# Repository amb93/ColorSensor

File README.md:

# Color sensor
A compact device that helps the blind and color blind to differentiate between colors. The devices shows the color on the top screen and has an AUX plug for voice. Fully rechargable, lasting over 10 hours.

# Work progress

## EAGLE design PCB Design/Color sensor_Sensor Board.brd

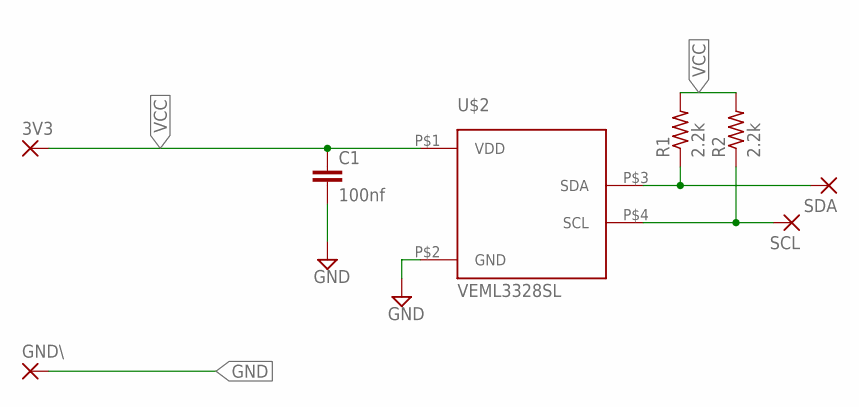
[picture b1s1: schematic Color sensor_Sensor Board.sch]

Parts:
3V3: SMD2; SMD1,27-2,54
C1: 100nf; C0805
GND\: SMD2; SMD1,27-2,54
R1, R2: 2.2k; R0805
SCL: SMD2; SMD1,27-2,54
SDA: SMD2; SMD1,27-2,54
U$2: VEML3328SL; OPLGA4SV

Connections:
GND: C1.2, GND\.1, U$2.P$2 (GND)
unnamed: R1.1, SDA.1, U$2.P$3 (SDA)
unnamed: R2.1, SCL.1, U$2.P$4 (SCL)
VCC: 3V3.1, C1.1, R1.2, R2.2, U$2.P$1 (VDD)

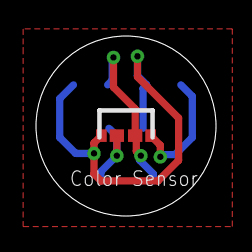
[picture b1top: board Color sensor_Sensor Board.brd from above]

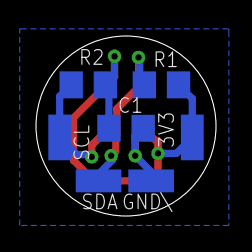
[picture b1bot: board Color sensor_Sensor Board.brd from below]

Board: 2 copper layers, 10.0 x 10.0 mm, 8 parts (7 on the bottom side), 4 nets.

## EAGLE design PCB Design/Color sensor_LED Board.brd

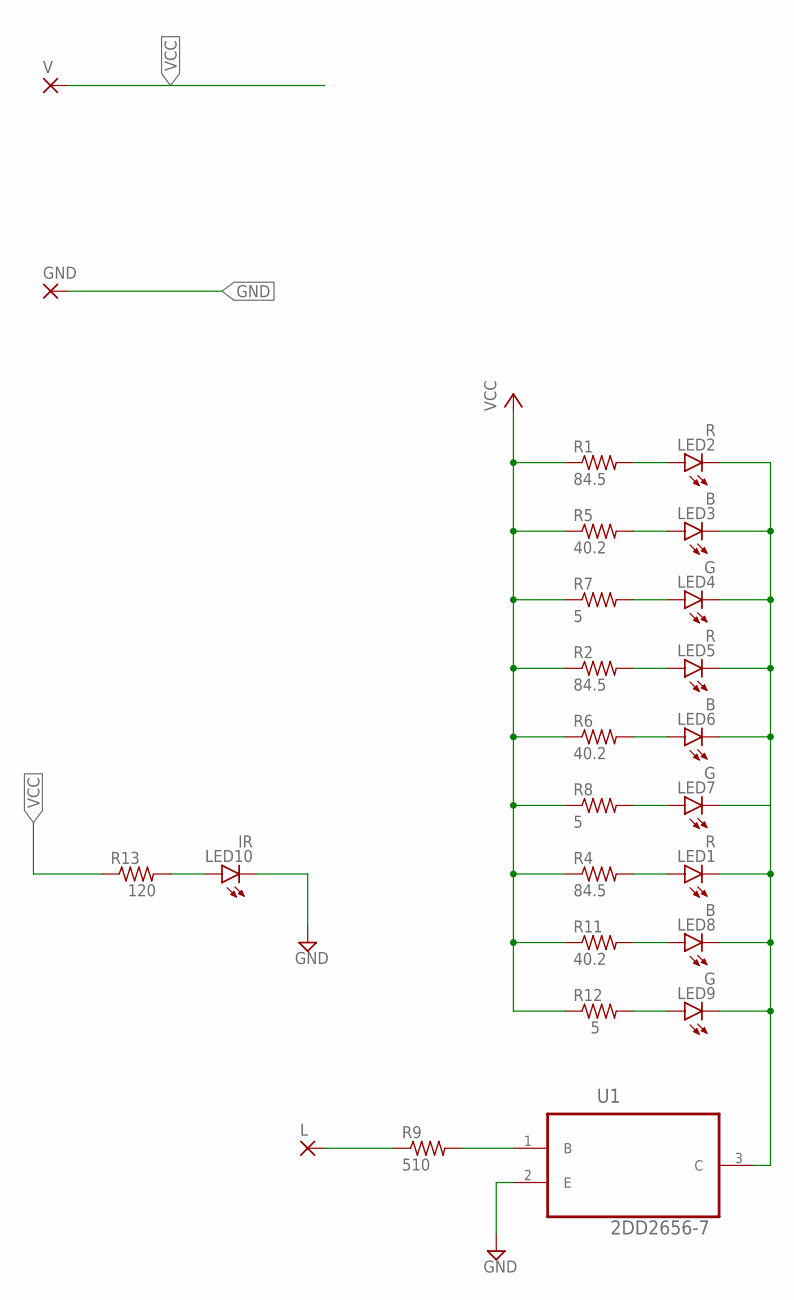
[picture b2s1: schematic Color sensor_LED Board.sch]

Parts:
GND: SMD2; SMD1,27-2,54
L: SMD2; SMD1,27-2,54
LED1, LED2, LED5: R; CHIPLED_0805
LED3, LED6, LED8: B; CHIPLED_0805
LED4, LED7, LED9: G; CHIPLED_0805
LED10: IR; CHIPLED_0805
R1, R2, R4: 84.5; R0805
R5, R6, R11: 40.2; R0805
R7, R8, R12: 5; R0805
R9: 510; R0805
R13: 120; R0805
U1: 2DD2656-7; SOT65P210X110-3N
V: SMD2; SMD1,27-2,54

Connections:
GND: GND.1, LED10.C, U1.2 (E)
unnamed: R9.2, U1.1 (B)
unnamed: L.1, R9.1
unnamed: LED2.A, R1.2
unnamed: LED3.A, R5.2
unnamed: LED4.A, R7.2
unnamed: LED5.A, R2.2
unnamed: LED6.A, R6.2
unnamed: LED7.A, R8.2
unnamed: LED1.A, R4.2
unnamed: LED8.A, R11.2
unnamed: LED9.A, R12.2
unnamed: LED1.C, LED2.C, LED3.C, LED4.C, LED5.C, LED6.C, LED7.C, LED8.C, LED9.C, U1.3 (C)
unnamed: LED10.A, R13.2
VCC: R1.1, R2.1, R4.1, R5.1, R6.1, R7.1, R8.1, R11.1, R12.1, R13.1, V.1

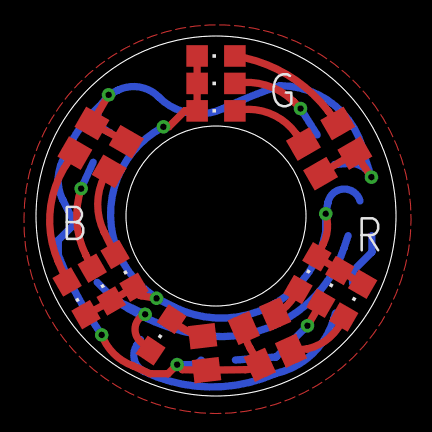
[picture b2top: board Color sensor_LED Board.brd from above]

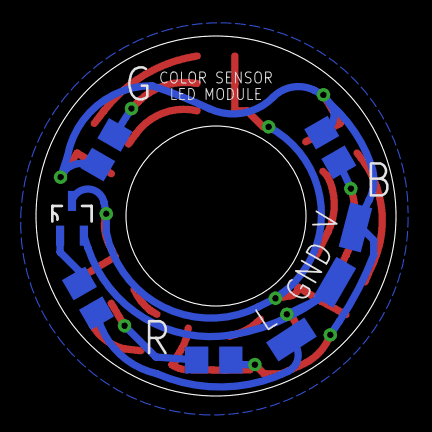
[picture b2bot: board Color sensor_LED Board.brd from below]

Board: 2 copper layers, 20.0 x 20.0 mm, 25 parts (8 on the bottom side), 15 nets.

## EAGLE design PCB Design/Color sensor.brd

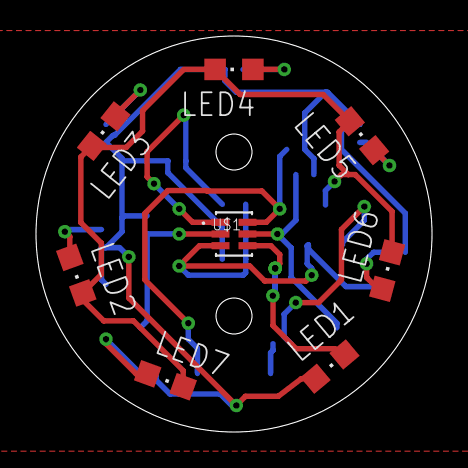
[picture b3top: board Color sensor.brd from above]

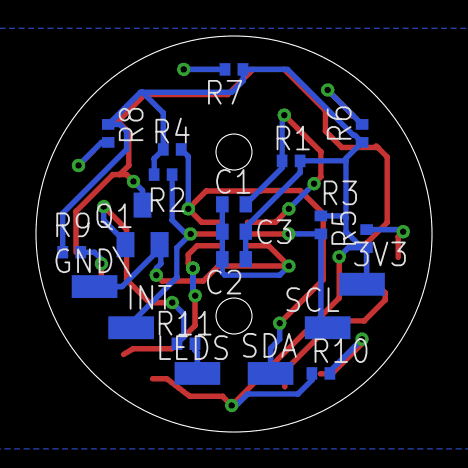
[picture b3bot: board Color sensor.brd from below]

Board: 2 copper layers, 22.0 x 22.0 mm, 29 parts (21 on the bottom side), 16 nets.

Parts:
3V3: SMD1,27-2,54
C1, C3: 1uf; C0402
C2: 22uf; C0402
GND\: SMD1,27-2,54
INT: SMD1,27-2,54
LED1: IR; CHIPLED_0805
LED2, LED5: RED; CHIPLED_0805
LED3, LED6: Blue; CHIPLED_0805
LED4, LED7: Green; CHIPLED_0805
LEDS: SMD1,27-2,54
Q1: BCV72SMD; SOT23-BEC
R1: 22; R0402
R2: 10k; R0402
R3, R4: 1.5k; R0402
R5, R6, R11: 75; R0402
R7, R8, R9, R10: 12; R0402
SCL: SMD1,27-2,54
SDA: SMD1,27-2,54
U$1: TCS37717FN; SON65P200X240X70-6N

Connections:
GND: C1.2, C2.2, C3.2, GND\.1, Q1.E, U$1.3
INT: INT.1, R2.1, U$1.5
LDR: LED1.C, U$1.4
unnamed: C1.1, R1.2, U$1.1
unnamed: Q1.B, R11.2
unnamed: LED2.C, LED3.C, LED4.C, LED5.C, LED6.C, LED7.C, Q1.C
unnamed: LEDS.1, R11.1
unnamed: LED2.A, R5.2
unnamed: LED3.A, R6.2
unnamed: LED4.A, R7.2
unnamed: LED5.A, R8.2
unnamed: LED6.A, R9.2
unnamed: LED7.A, R10.2
SCL: R3.1, SCL.1, U$1.2
SDA: R4.1, SDA.1, U$1.6
VCC: 3V3.1, C2.1, C3.1, LED1.A, R1.1, R2.2, R3.2, R4.2, R5.1, R6.1, R7.1, R8.1, R9.1, R10.1

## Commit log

2022-01-11 Uploaded PCB design
2022-01-11 Arduino libary added as a submodule
2022-01-15 corrected unconnected traces and IR LED problem
2022-01-28 added arduino code
2022-01-28 added hue conversion
2022-01-31 added value and saturation
2022-08-18 Project finished
